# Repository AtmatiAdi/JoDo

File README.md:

# Opis projektu

Głównym celem projektu jest stworzenie Joystick'a na bazie mikrokontrolera STM32F103. Założeniem jest aby uniwersalnym urządzeniem można było sterować różnymi robotami przez moduł Bluetooth lub WIFI, oraz tradycyjnie obsługiwać komputer poprzez interfejs USB jako joystick lub jako mysz. Ma on posiadać niżej opisane funkcjonalności:

* Baterie do pracy bez zasilania przewodowego.
* Zintegrowaną ładowarkę i kontrolę napięcia baterii.
* Gałkę precyzyjną i  szereg przycisków do kontroli i sterowania.
* Akcelerometr do różnego rodzaju kontroli lub jako kolejna “gałka joysticka”.
* Interfejs USB umożliwiający podłączenie do komputera jako urządzenie HID jak i ładowanie samego urządzenia.
* Moduł Bluetooth, WIFI i radiowy umożliwiający implementację sterowania różnego rodzaju robotami.

Mikrokontroler STM32F103 przez magistralę UART komunikować się będzie z modułem WIFI i modułem Bluetooth HC-05 aby umożliwić podłączenie i sterowanie innym urządzeniem. Moduł HC-05 jest programowalny (komendami AT można zmienić częstotliwość komunikacji i tryb pracy master/slave). Moduł komunikacji radiowej nRF24L01+ jest zasilany napięciem 1.9 - 3.6 V. Może pracować w trybie nadajnika i odbiornika. Wyświetlacz oled służy do wyświetlania informacji takich jak stan połączenia, informacje zwrotne z urządzenia, stan baterii itp. Przetwornica ma możliwość wyłączenia w przypadku rozładowania baterii, tym zarządza mikrokontroler. Głównym zadaniem będzie działanie jako joystick po podłączeniu do komputera przez USB. Moduł IMU służy jako kontroler tak jak sam joystick. Architektura systemu:

# Opis działania programu

Uniwersalność urządzenia zapewniona jest poprzez możliwość wybierania trybów pracy. Tryb wybierany jest z menu  uruchamianego po włączeniu urządzenia. Do nawigacji po menu służą niebieskie przyciski - skrajne do zmiany opcji, a środkowy do zatwierdzenia. Podstawowym trybem jest praca jako gamepad, dodatkowo jednak na potrzeby projektu robota micromouse dodano tryb pracy jako mostek pomiędzy robotem a komputerem. W miarę potrzeb program można rozszerzyć o kolejne funkcje trybów z odpowiednio skonfigurowanymi peryferiami, w zależności od wymagań projektu. Program urządzenia podzielony jest na funkcje programów i na funkcje główne. Funkcje główne są odpowiedzialne za kontrolę urządzenia i inicjalizację modułów. Funkcje programów dzielą się na dwa typy: inicjalizacji i pętli, inicjalizacja wybranego programu sprowadza się do wywołania funkcji inicjalizujących moduły i~peryferia dostarczone przez funkcje główne, jest to umowny poziom abstrakcji. Funkcja petli programu jest rdzeniem programu, nie powinna ona byc nieskończoną pętlą, gdyz sama będzie wywoływana w takiej pętli, wraz z funkcją Update która odpowiedzialna jest za kontrolę baterii i zasilania. Program został zrealizowany w taki sposób, ponieważ nie można jednocześnie skonfigurować HID i interfejsu szeregowego, dalsze projekty mogły by powodowac inne konflikty. Wybór innego trybu pracy możliwy jest jedynie po zresetowaniu urządzenia.

# Linki 

https://youtu.be/tafsixhDsh8 - Prezentacja ukończenia projektu

https://www.overleaf.com/read/fwncyzqsmkhw - Raport końcowy

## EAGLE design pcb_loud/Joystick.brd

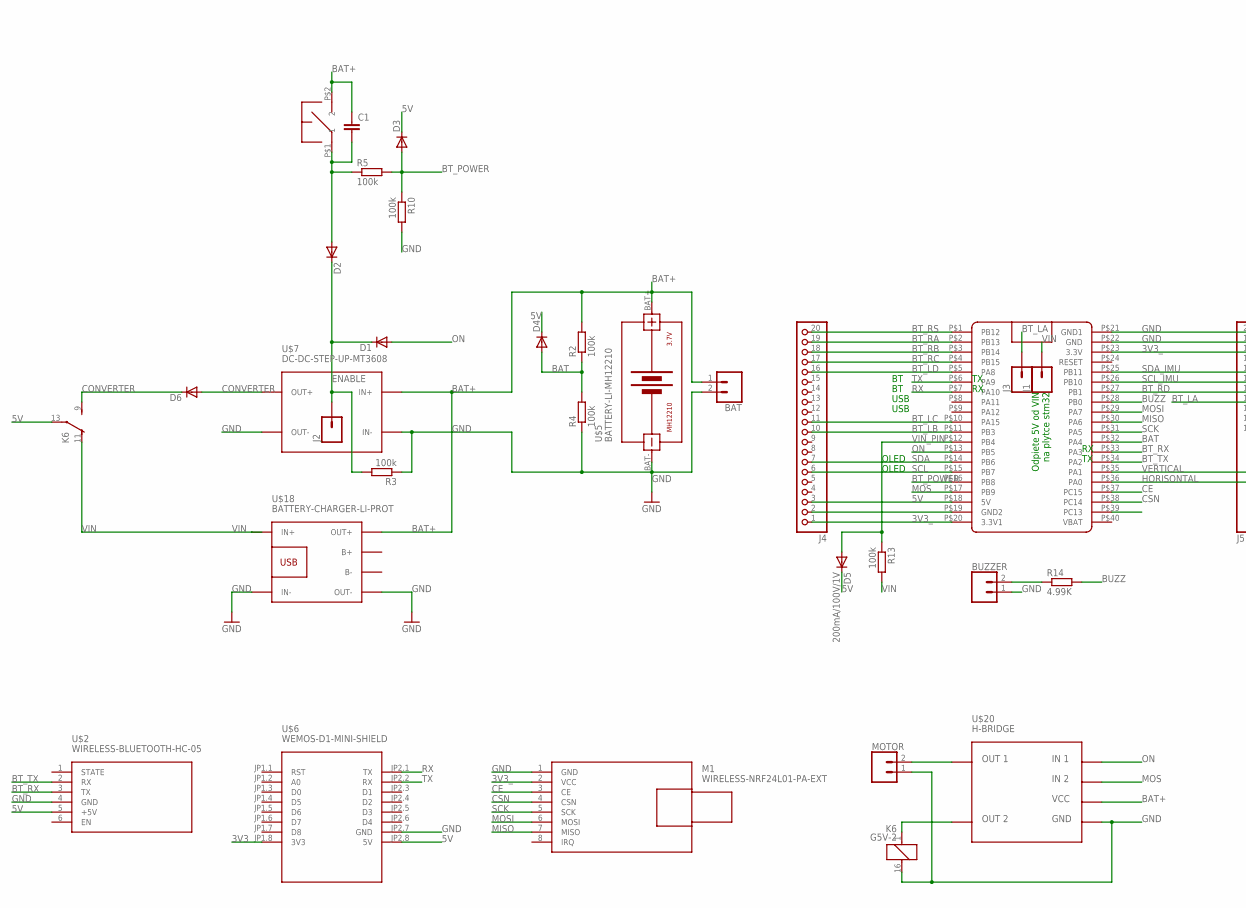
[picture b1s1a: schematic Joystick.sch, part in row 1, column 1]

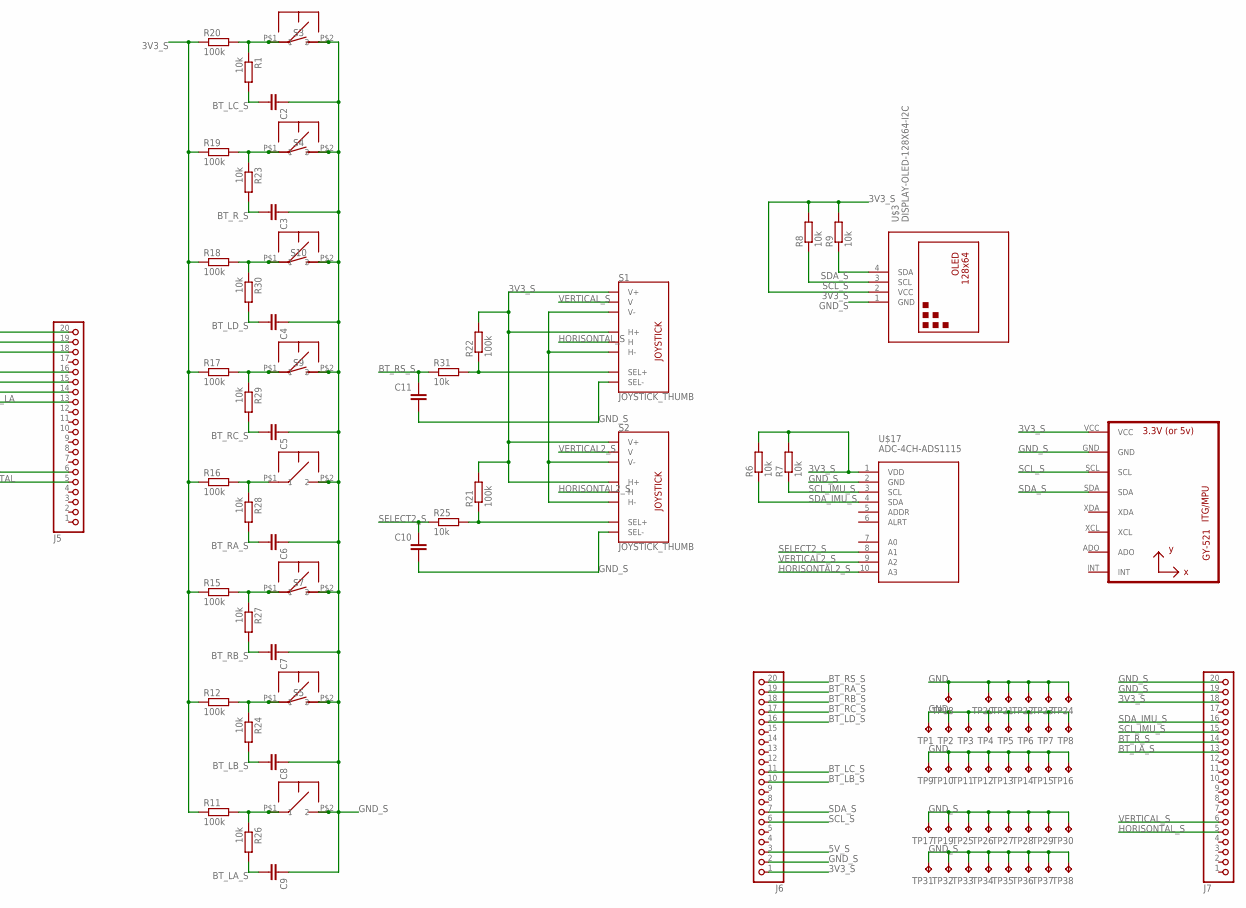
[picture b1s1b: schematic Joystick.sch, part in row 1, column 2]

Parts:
BAT: CONN_02; 1X02
BUZZER: CONN_02; 1X02
C1, C2, C3, C4, C5, C6, C7, C8, C9, C10, C11: C-EUC1206; C1206
D1, D2, D3, D4, D5, D6: 200mA/100V/1V; DO214AC
J1, J2, J3: CONN_01; 1X01
J4, J5, J6, J7: PINHD-1X20; 1X20
K6: G5V-2
M1: WIRELESS-NRF24L01-PA-EXT
MOTOR: CONN_02; 1X02
R1, R6, R7, R8, R9, R23, R24, R25, R26, R27, R28, R29, R30, R31: 10k; R0805
R2, R3, R4, R5, R10, R11, R12, R13, R15, R16, R17, R18, R19, R20, R21, R22: 100k; R0805
R14: 4.99K; R0805
S1, S2: JOYSTICK_THUMB; JOYSTICK
S3, S4, S5, S7, S9, S10: MOMENTARY-SWITCH-SPST-PTH-12MM; TACTILE_SWITCH_PTH_12MM
TP1, TP2, TP3, TP4, TP5, TP6, TP7, TP8, TP9, TP10, TP11, TP12, TP13, TP14, TP15, TP16, TP17, TP18, TP19, TP20, TP21, TP22, TP23, TP24, TP25, TP26, TP27, TP28, TP29, TP30, TP31, TP32, TP33, TP34, TP35, TP36, TP37, TP38: TPB1,27; B1,27
U1: GY-521MPU6050; GY-521
U$1: BLUE_PILL
U$2: WIRELESS-BLUETOOTH-HC-05
U$3: DISPLAY-OLED-128X64-I2C
U$4, U$8, U$9, U$10, U$11, U$12, U$13, U$14, U$16: MOUSE_BT
U$5: BATTERY-LI-MH12210
U$6: WEMOS-D1-MINI-SHIELD
U$7: DC-DC-STEP-UP-MT3608
U$17: ADC-4CH-ADS1115
U$18: BATTERY-CHARGER-LI-PROT

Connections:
3V3: U$6.JP1.8 (3V3)
3V3_: J4.1, J5.18, M1.2 (VCC), U$1.P$20 (3.3V1), U$1.P$23 (3.3V)
3V3_S: J6.1, J7.18, R6.2, R7.2, R8.2, R9.2, R11.1, R12.1, R15.1, R16.1, R17.1, R18.1, R19.1, R20.1, R21.2, R22.2, S1.H1 (H+), S1.V1 (V+), S2.H1 (H+), S2.V1 (V+), U1.VCC, U$3.2 (VCC), U$17.1 (VDD)
5V: D3.C, D4.C, D5.C, J4.3, K6.13, U$1.P$18 (5V), U$2.5 (+5V), U$6.JP2.8 (5V)
5V_S: J6.3
ASD: BUZZER.2, R14.1
BAT: D4.A, R2.1, R4.2, U$1.P$32 (PA4)
BAT+: BAT.1, C1.1, R2.2, U$5.BAT+, U$7.IN+, U$8.P$2 (2), U$18.OUT+
BT_LA: J3.1, J5.13
BT_LA_S: C9.2, J7.13, R26.2
BT_LB: J4.10, U$1.P$11 (PB3)
BT_LB_S: C8.2, J6.10, R24.2
BT_LC: J4.11, U$1.P$10 (PA15)
BT_LC_S: C2.2, J6.11, R1.2
BT_LD: J4.16, U$1.P$5 (PA8)
BT_LD_S: C4.2, J6.16, R30.2
BT_POWER: D3.A, R5.2, R10.1, U$1.P$16 (PB8)
BT_RA: J4.19, U$1.P$2 (PB13)
BT_RA_S: C6.2, J6.19, R28.2
BT_RB: J4.18, U$1.P$3 (PB14)
BT_RB_S: C7.2, J6.18, R27.2
BT_RC: J4.17, U$1.P$4 (PB15)
BT_RC_S: C5.2, J6.17, R29.2
BT_RD: J5.14, U$1.P$27 (PB1)
BT_RS: J4.20, U$1.P$1 (PB12)
BT_RS_S: C11.1, J6.20, R31.1
BT_RX: U$1.P$33 (PA3), U$2.3 (TX)
BT_R_S: C3.2, J7.14, R23.2
BT_TX: U$1.P$34 (PA2), U$2.2 (RX)
BUTTON: C1.2, D2.A, R5.1, U$8.P$1 (1)
BUZZ: R14.2, U$1.P$28 (PB0)
CE: M1.3 (CE), U$1.P$37 (PC15)
CONVERTER: D6.C, K6.9 (S)
CSN: M1.4 (CSN), U$1.P$38 (PC14)
ENABLE: D1.C, D2.C, J2.1, R3.2
GGJHGJ: U$1.P$39 (PC13)
GND: BAT.2, BUZZER.1, J4.2, J5.19, J5.20, K6.16 (2), M1.1 (GND), MOTOR.1, R3.1, R4.1, R10.2, TP1.TP, TP2.TP, TP3.TP, TP4.TP, TP5.TP, TP6.TP, TP7.TP, TP8.TP, TP9.TP, TP10.TP, TP11.TP, TP12.TP, TP13.TP, TP14.TP, TP15.TP, TP16.TP, TP18.TP, TP20.TP, TP21.TP, TP22.TP, TP23.TP, TP24.TP, U$1.P$19 (GND2), U$1.P$21 (GND1), U$1.P$22 (GND), U$2.4 (GND), U$5.BAT-, U$6.JP2.7 (GND), U$7.IN-, U$7.OUT-, U$18.IN-, U$18.OUT-
GND_S: C2.1, C3.1, C4.1, C5.1, C6.1, C7.1, C8.1, C9.1, C10.2, C11.2, J6.2, J7.19, J7.20, S1.B2A (SEL-), S1.H3 (H-), S1.V3 (V-), S2.B2A (SEL-), S2.H3 (H-), S2.V3 (V-), S3.3 (2), S4.3 (2), S5.3 (2), S7.3 (2), S9.3 (2), S10.3 (2), TP17.TP, TP19.TP, TP25.TP, TP26.TP, TP27.TP, TP28.TP, TP29.TP, TP30.TP, TP31.TP, TP32.TP, TP33.TP, TP34.TP, TP35.TP, TP36.TP, TP37.TP, TP38.TP, U1.GND, U$3.1 (GND), U$4.P$2 (2), U$9.P$2 (2), U$10.P$2 (2), U$11.P$2 (2), U$12.P$2 (2), U$13.P$2 (2), U$14.P$2 (2), U$16.P$2 (2), U$17.2 (GND)
HORISONTAL: J5.5, U$1.P$36 (PA0)
HORISONTAL2_S: S2.H2 (H), U$17.10 (A3)
HORISONTAL_S: J7.5, S1.H2 (H)
MISO: M1.7 (MISO), U$1.P$30 (PA6)
MOS: U$1.P$17 (PB9)
MOSI: M1.6 (MOSI), U$1.P$29 (PA7)
unnamed: D6.A, U$7.OUT+
unnamed: R1.1, R20.2, S3.1, U$10.P$1 (1)
unnamed: R19.2, R23.1, S4.1, U$4.P$1 (1)
unnamed: R21.1, R25.2, S2.B1A (SEL+)
unnamed: R12.2, R24.1, S5.1, U$11.P$1 (1)
unnamed: R11.2, R26.1, U$9.P$1 (1)
unnamed: R18.2, R30.1, S10.1, U$16.P$1 (1)
unnamed: R17.2, R29.1, S9.1, U$14.P$1 (1)
unnamed: R16.2, R28.1, U$12.P$1 (1)
unnamed: R15.2, R27.1, S7.1, U$13.P$1 (1)
unnamed: R22.1, R31.2, S1.B1A (SEL+)
ON: D1.A, U$1.P$13 (PB5)
RX: U$1.P$7 (PA10), U$6.JP2.1 (TX)
SCK: M1.5 (SCK), U$1.P$31 (PA5)
SCL: J4.6, U$1.P$15 (PB7)
SCL_IMU: J5.15, U$1.P$26 (PB10)
SCL_IMU_S: J7.15, R7.1, U$17.3 (SCL)
SCL_S: J6.6, R8.1, U1.SCL, U$3.3 (SCL)
SDA: J4.7, U$1.P$14 (PB6)
SDA_IMU: J5.16, U$1.P$25 (PB11)
SDA_IMU_S: J7.16, R6.1, U$17.4 (SDA)
SDA_S: J6.7, R9.1, U1.SDA, U$3.4 (SDA)
SELECT2_S: C10.1, R25.1, U$17.8 (A1)
TX: U$1.P$6 (PA9), U$6.JP2.2 (RX)
VERTICAL: J5.6, U$1.P$35 (PA1)
VERTICAL2_S: S2.V2 (V), U$17.9 (A2)
VERTICAL_S: J7.6, S1.V2 (V)
VIN: J1.1, K6.11 (O), R13.2, U$18.IN+
VIN_PIN: D5.A, R13.1, U$1.P$12 (PB4)

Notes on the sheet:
Odpiete 5V od VIN na plytce stm32
USB
OLED
H-BRIDGE
U$20
IN 1
IN 2
OUT 1
OUT 2
VCC
GND

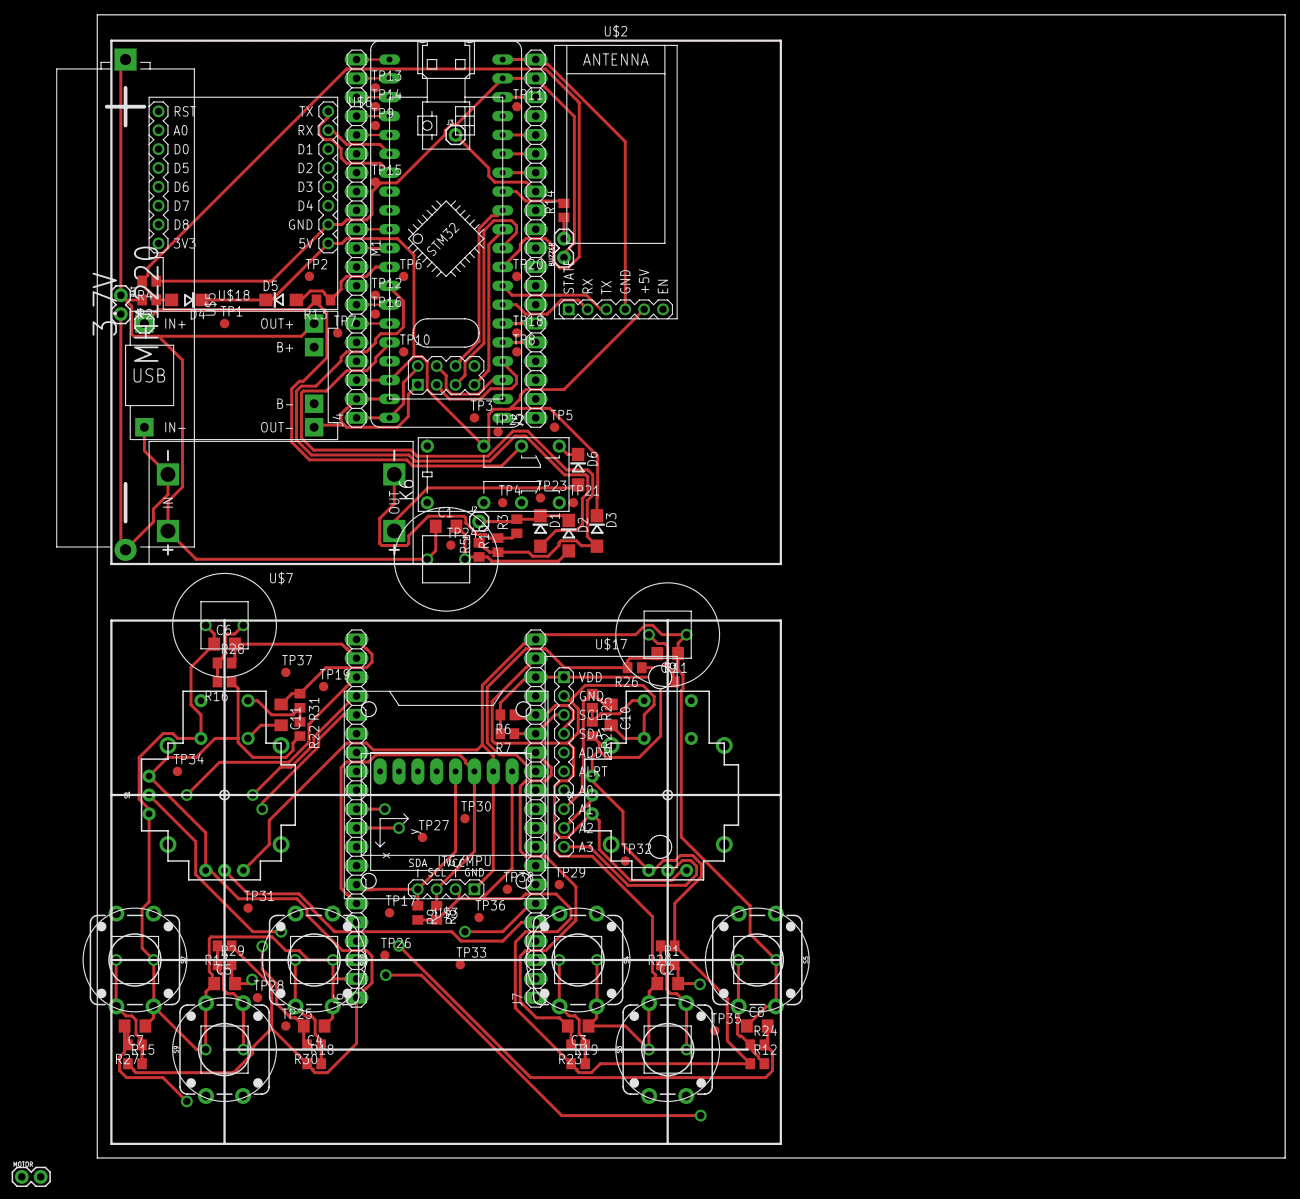
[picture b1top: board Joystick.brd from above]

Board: 4 copper layers, 160.0 x 154.0 mm, 124 parts (0 on the bottom side), 69 nets.

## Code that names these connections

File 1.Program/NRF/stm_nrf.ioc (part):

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Mcu.Name=STM32F103C(8-B)Tx
Mcu.Package=LQFP48
Mcu.UserName=STM32F103CBTx
PA0-WKUP.GPIOParameters=GPIO_Label
PA0-WKUP.GPIO_Label=HORISONTAL
PA0-WKUP.Signal=ADCx_IN0
PA1.GPIOParameters=GPIO_Label
PA1.GPIO_Label=VERTICAL
PA1.Signal=ADCx_IN1
PA10.Mode=Asynchronous
PA10.Signal=USART1_RX
PA11.Mode=Device
PA11.Signal=USB_DM
PA12.Mode=Device
PA12.Signal=USB_DP
PA13.Mode=Serial_Wire
PA13.Signal=SYS_JTMS-SWDIO
PA14.Mode=Serial_Wire
PA14.Signal=SYS_JTCK-SWCLK
PA15.GPIOParameters=GPIO_Label
PA15.GPIO_Label=BT_LC
PA15.Signal=GPIO_Input
PA2.GPIOParameters=GPIO_Label
PA2.GPIO_Label=BT_TX
PA2.Mode=Asynchronous
PA2.Signal=USART2_TX
PA3.GPIOParameters=GPIO_Label
PA3.GPIO_Label=BT_RX
PA3.Mode=Asynchronous
PA3.Signal=USART2_RX
PA4.GPIOParameters=GPIO_Label
PA4.GPIO_Label=BAT
PA4.Signal=ADCx_IN4
PA5.Mode=Full_Duplex_Master
PA5.Signal=SPI1_SCK
PA6.Mode=Full_Duplex_Master
PA6.Signal=SPI1_MISO
PA7.Mode=Full_Duplex_Master
PA7.Signal=SPI1_MOSI
PA8.GPIOParameters=GPIO_Label
PA8.GPIO_Label=BT_RD
PA8.Signal=GPIO_Input
PA9.Mode=Asynchronous
PA9.Signal=USART1_TX
PB0.GPIOParameters=GPIO_Label
PB0.GPIO_Label=BUZZ
PB0.Signal=S_TIM3_CH3
PB1.GPIOParameters=GPIO_Label
PB1.GPIO_Label=BT_LD
PB1.Signal=GPIO_Input
PB10.GPIOParameters=GPIO_Label
PB10.GPIO_Label=SCL_IMU
PB10.Mode=I2C
PB10.Signal=I2C2_SCL
PB11.GPIOParameters=GPIO_Label
PB11.GPIO_Label=SDA_IMU
PB11.Mode=I2C
PB11.Signal=I2C2_SDA
PB12.GPIOParameters=GPIO_Label
PB12.GPIO_Label=BT_RS
PB12.Signal=GPIO_Input
PB13.GPIOParameters=GPIO_Label
PB13.GPIO_Label=BT_RA
PB13.Signal=GPIO_Input
PB14.GPIOParameters=GPIO_Label
PB14.GPIO_Label=BT_RB
PB14.Signal=GPIO_Input
PB15.GPIOParameters=GPIO_Label
PB15.GPIO_Label=BT_RC
PB15.Signal=GPIO_Input
PB2.GPIOParameters=GPIO_Label
PB2.GPIO_Label=BT_LA
PB2.Signal=GPIO_Input
PB3.GPIOParameters=GPIO_Label
PB3.GPIO_Label=BT_LB
PB3.Signal=GPIO_Input
PB4.GPIOParameters=GPIO_Label
PB4.GPIO_Label=VIN
PB4.Signal=GPIO_Input
PB5.GPIOParameters=GPIO_Label
PB5.GPIO_Label=ON
PB5.Signal=GPIO_Output
PB6.GPIOParameters=GPIO_Label
PB6.GPIO_Label=SCL
PB6.Mode=I2C
PB6.Signal=I2C1_SCL
PB7.GPIOParameters=GPIO_Label
PB7.GPIO_Label=SDA
PB7.Mode=I2C
PB7.Signal=I2C1_SDA
PB8.GPIOParameters=GPIO_Label
PB8.GPIO_Label=BT_POWER
PB8.Signal=GPIO_Input
PB9.GPIOParameters=GPIO_Label
PB9.GPIO_Label=MOS
PB9.Signal=GPIO_Output
PC13-TAMPER-RTC.GPIOParameters=GPIO_Label
PC13-TAMPER-RTC.GPIO_Label=LED
PC13-TAMPER-RTC.Signal=GPIO_Output
PC14-OSC32_IN.GPIOParameters=GPIO_Label
PC14-OSC32_IN.GPIO_Label=CSN
PC14-OSC32_IN.Signal=GPIO_Output
PC15-OSC32_OUT.GPIOParameters=GPIO_Label
PC15-OSC32_OUT.GPIO_Label=CE
PC15-OSC32_OUT.Signal=GPIO_Output
PD0-OSC_IN.Mode=HSE-External-Oscillator
PD0-OSC_IN.Signal=RCC_OSC_IN
PD1-OSC_OUT.Mode=HSE-External-Oscillator
PD1-OSC_OUT.Signal=RCC_OSC_OUT
RCC.SYSCLKFreq_VALUE=72000000
RCC.SYSCLKSource=RCC_SYSCLKSOURCE_PLLCLK
board=custom

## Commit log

2020-05-14 Wprowadzono projekt
2020-05-18 Dodano przesył funkcji
2020-06-01 Zmiany
2020-06-01 pomieszanie bibliotek
2020-06-01 tak samo
2020-06-01 Naprawione
2020-06-05 dodanie bibliotek
2020-06-06 dodanie komentarzy
2020-06-06 konfiguracja HID
2020-06-10 Dodano elementy do guzikow
2020-06-10 Poprawiono program HID
2020-06-12 funkcja noBlink
2020-06-12 funkcje wyboru programow
2020-06-12 menu programy
2020-06-12 grafika przy starcie
2020-06-12 biblioteki
2020-06-12 poprawki
2020-06-12 Poprawa
2020-06-12 poprawienie bledow

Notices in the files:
parts and their libraries:
SparkFun-Connectors: Licensing: Creative Commons ShareAlike 4.0 International - https://creativecommons.org/licenses/by-sa/4.0
diy-modules: Released under the Creative Commons Attribution 4.0 International License: http://creativecommons.org/licenses/by/4.0
